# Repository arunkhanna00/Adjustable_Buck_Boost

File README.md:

# Adjustable Flyback Converter
Built a DC-DC converter that can step-down/step-up a voltage based on the LM2587.

It has the option to:
- current limiting option
- single split voltage rail

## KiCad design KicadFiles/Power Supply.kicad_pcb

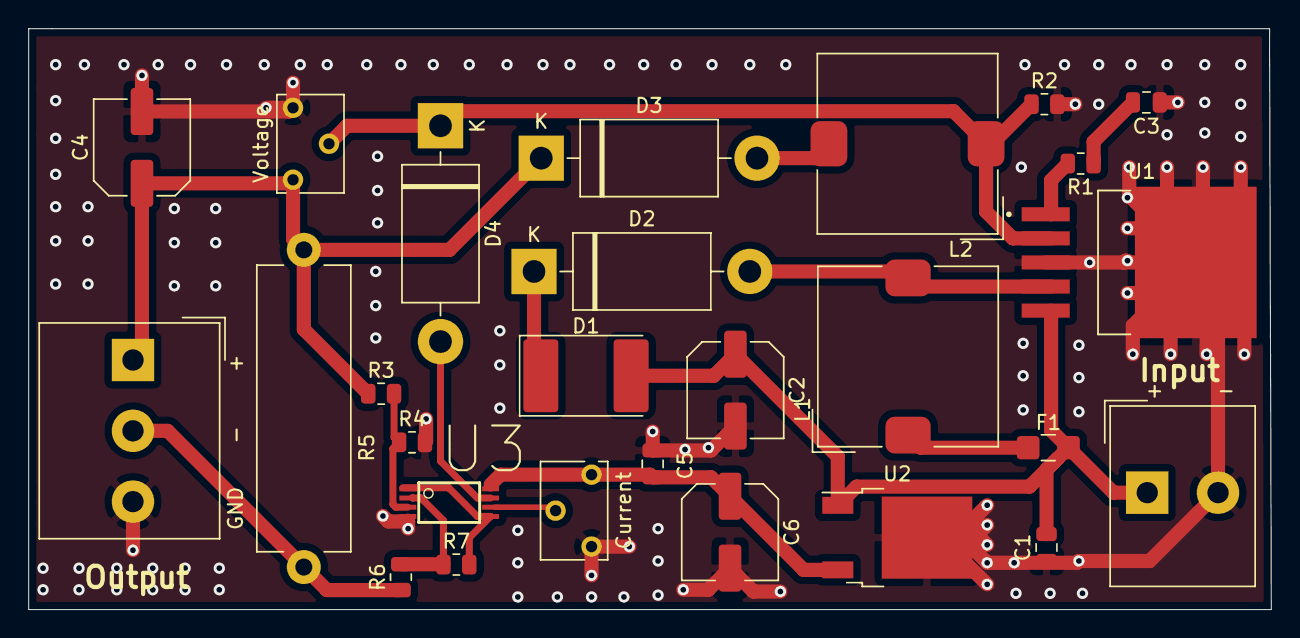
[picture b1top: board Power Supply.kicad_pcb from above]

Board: 2 copper layers, 87.8 x 41.0 mm, 27 parts (0 on the bottom side), 17 nets.

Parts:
+     -: Input; Altech_AK300_1x02_P5.00mm_45-Degree
C1, C3: 1uF; C_0805_2012Metric
C2: 220uF; C_Elec_6.3x5.4
C4: 220uF; C_Elec_6.3x5.8
C5: 10n; C_0805_2012Metric
C6: 10u; C_Elec_6.3x5.8
Current: 10k; Potentiometer_Bourns_3266W_Vertical
D1: D_Schottky; D_3220_8050Metric
D2: MUR120; D_DO-201AD_P15.24mm_Horizontal
D3, D4: MBR340; D_DO-201AD_P15.24mm_Horizontal
F1: 2 A; Fuse_1206_3216Metric_Castellated
GND    -     +: Output; Altech_AK300_1x03_P5.00mm_45-Degree
L1, L2: 100uH; L_TDK_SLF12565
R1: 3k; R_0805_2012Metric
R2: 2k; R_0805_2012Metric
R3, R6: 3.3k; R_0805_2012Metric
R4, R7: 100k; R_0805_2012Metric
R5: 0.1; R_Axial_Power_L20.0mm_W6.4mm_P22.40mm
U1: LM2587S-ADJ; VREG_TPS79625KTTR
U2: LF33_TO252; TO-252-2
U3: M; MCP602
Voltage: 10k; Potentiometer_Bourns_3266W_Vertical

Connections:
+3V3: C5.1, C6.1, Current.3, U2.3, U3.8
+BATT: + -.1, C1.2, C2.1, D1.2, F1.2, U1.5, U2.1
+VDC: C4.1, D3.1, GND - +.1, R3.1, R5.2, Voltage.3
-VDC: GND - +.2, R5.1, R6.1
CurrentLimiter: D4.1, L2.1, R2.1, U1.2, Voltage.2
GND: + -.2, C1.1, C2.2, C3.1, C4.2, C5.2, C6.2, Current.1, GND - +.3, R2.2, R4.2, U1.3, U1.6, U2.2, U3.4, Voltage.1
unnamed: C3.2, R1.1
unnamed: D1.1, D2.1
unnamed: D2.2, L1.2, U1.4
unnamed: D3.2, L2.2
unnamed: D4.2, U3.7
unnamed: F1.1, L1.1
unnamed: R1.2, U1.1
unnamed: R3.2, R4.1, U3.3
unnamed: R6.2, R7.1, U3.2
unnamed: R7.2, U3.1, U3.5
unnamed: Current.2, U3.6

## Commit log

2021-08-31 Kicad Files
